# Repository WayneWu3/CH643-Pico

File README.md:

# CH643-Pico

## Introduction
The ch643-pico is a development board based on the WCH CH643Q 32-bit RISC-V MCU. It provides a compact and breadboard-friendly platform for USB Type-C and Power Delivery applications.

## Hardware Resources
*   **MCU**: WCH CH643Q featuring the QingKe-V4C RISC-V core.
*   **Interface**: USB Type-C port for power delivery and data communication.
*   **Power**: Dual power input support with 3.3V regulated output.
*   **Control**: Two user buttons and status LEDs for power and communication monitoring.
*   **Debug**: Dedicated pin headers for UART and SWD interfaces.

## Pin Definitions
| Pin | Label  | Function                   |
| :-- | :----- | :------------------------- |
| 1   | 3.3V   | 3.3V Power Output          |
| 2   | 3.3V   | 3.3V Power Output          |
| 3   | GND    | GND                        |
| 4   | PA23   | TIM2_CH3N                  |
| 5   | PA1    | TIM2_CH2/ADC_IN1           |
| 6   | PA2    | USART2_TX/TIM2_CH3/ADC_IN2 |
| 7   | PA3    | USART2_RX/TIM2_CH4/ADC_IN3 |
| 8   | GND    | GND                        |
| 9   | PA5    | SPI0_SCK/ADC_IN5           |
| 10  | PA6    | SPI0_MISO/TIM3_CH1/ADC_IN6 |
| 11  | PA7    | SPI0_MOSI/TIM3_CH2/ADC_IN7 |
| 12  | PB0    | USART4_TX/ADC_IN8          |
| 13  | PB1    | USART4_RX/ADC_IN9          |
| 14  | PB2    | TIM1_CH2N                  |
| 15  | PB3    | TIM1_CH3N                  |
| 16  | PB4    | GPIO                       |
| 17  | PB6    | TIM1_CH1N/USART3_CTS       |
| 18  | PB7    | TIM1_CH2N/USART3_RTS       |
| 19  | PB8    | TIM1_CH3N                  |
| 20  | PB9    | TIM1_CH1/MCO               |
| 21  | EXT_5V | 5V Power Input             |
| 22  | EXT_5V | 5V Power Input             |
| 23  | GND    | GND                        |
| 24  | 3.3V   | 3.3V Power Output          |
| 25  | EXT_5V | 5V Power Input             |
| 26  | PA21   | TIM2_CH1N                  |
| 27  | PA20   | TIM2_BK                    |
| 28  | GND    | GND                        |
| 29  | PA19   | TIM2_ETR                   |
| 30  | PA15   | GPIO                       |
| 31  | 3.3V   | 3.3V Power Output          |
| 32  | PA11   | I2C_SDA                    |
| 33  | GND    | GND                        |
| 34  | PA10   | I2C_SCL                    |
| 35  | PA8    | USART4_RTS                 |
| 36  | PB15   | USART4_CTS                 |
| 37  | PB23   | GPIO                       |
| 38  | GND    | GND                        |
| 39  | PB21   | GPIO                       |
| 40  | PB14   | GPIO                       |

## Onboard Peripherals
| Component   | Pin  | Logic       |
| :---------- | :--- | :---------- |
| KEY1 | PB12 | Active Low  |
| KEY2 | PB16 | Active Low  |
| LED | PB17 | Active Low |

## Functional Features
*   **Power Path**: Integrated Schottky diodes protect the circuit when using both USB and external power sources.
*   **ESD Protection**: USB data and configuration channel lines are equipped with protection arrays to ensure hardware durability.
*   **Logic Level**: All I/O signals are 3.3V compatible.

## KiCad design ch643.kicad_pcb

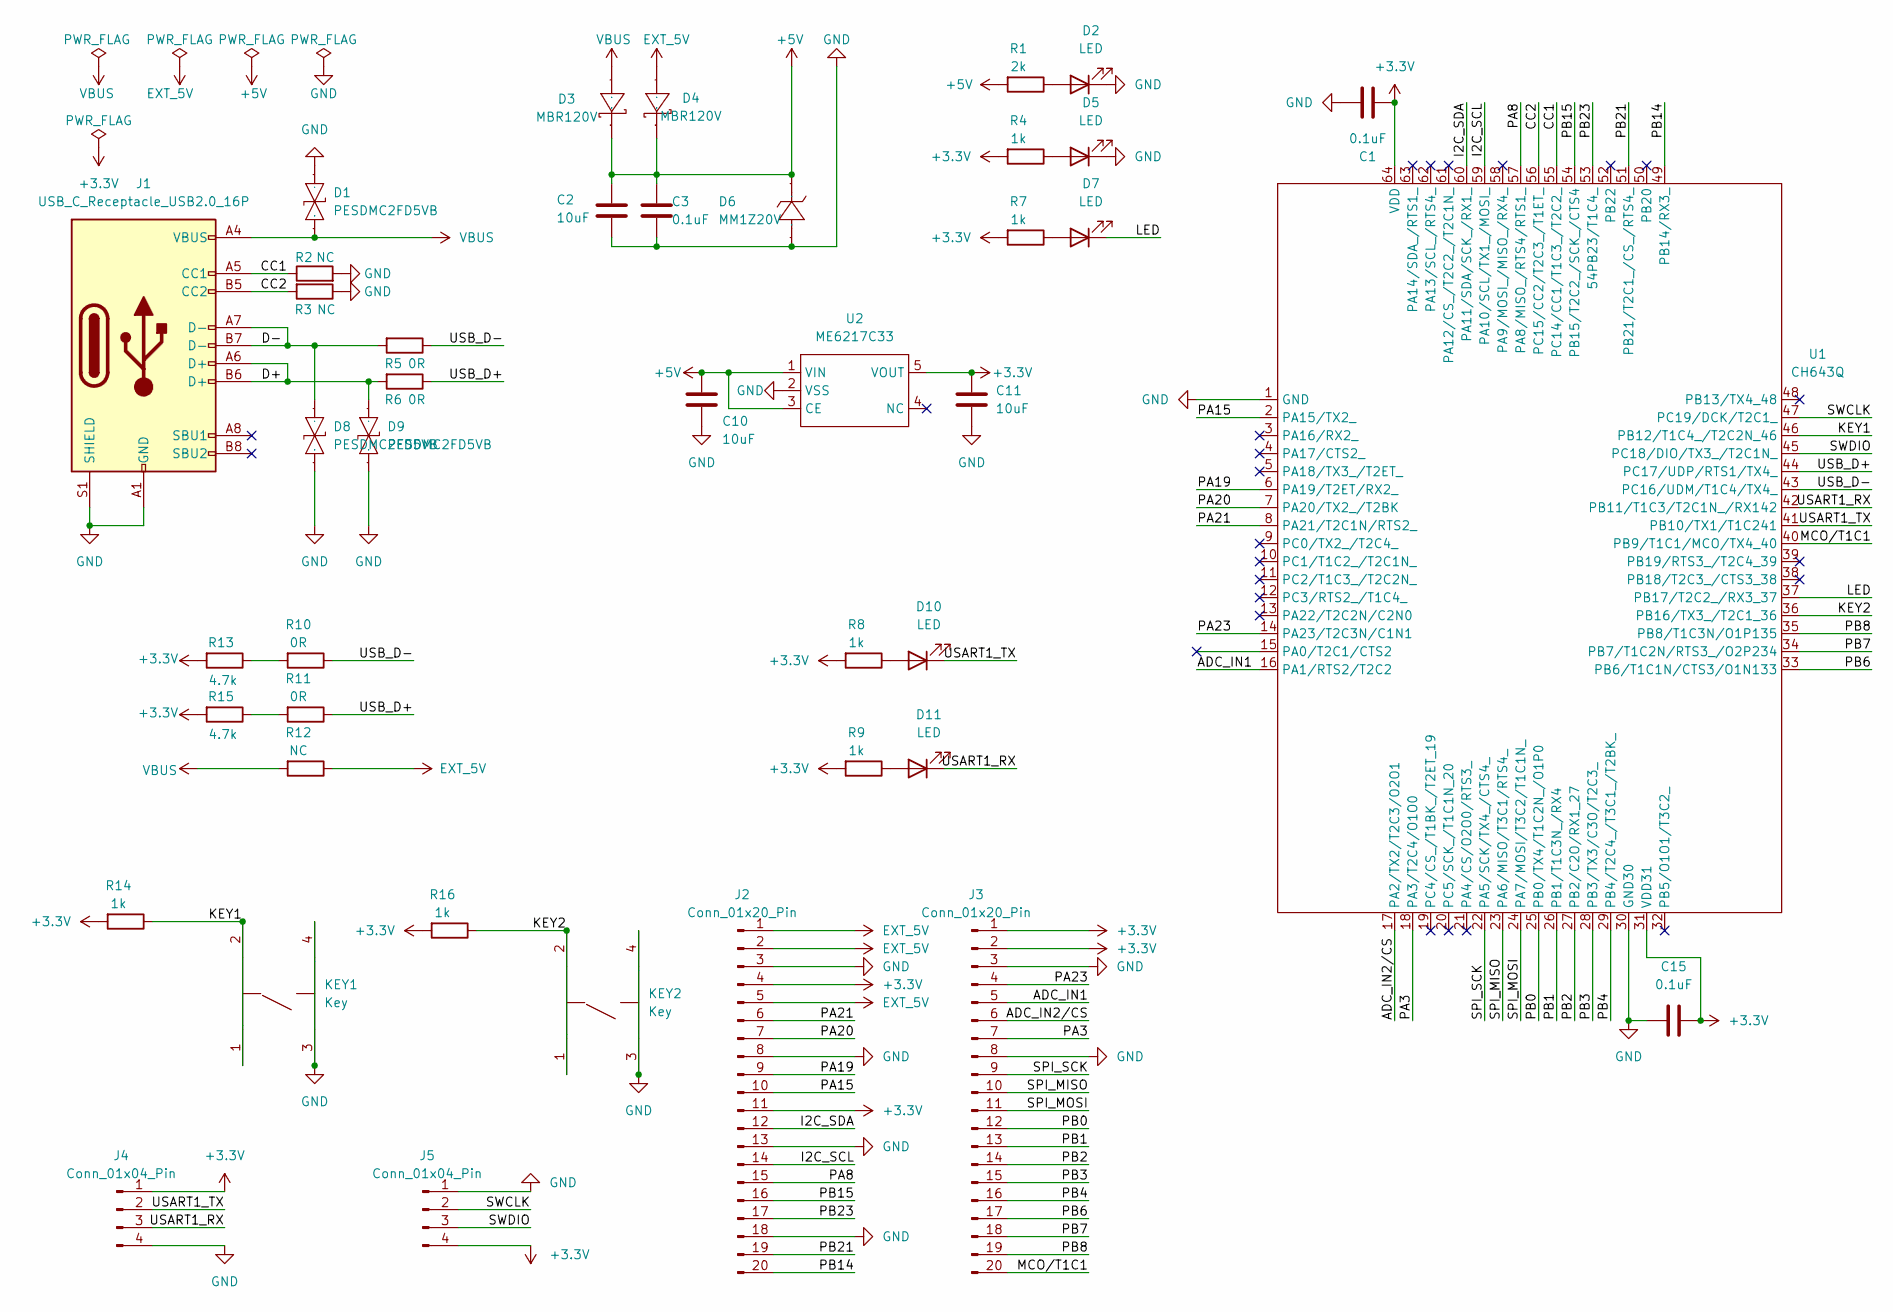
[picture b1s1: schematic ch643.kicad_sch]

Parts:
C1, C15: 0.1uF; C_0402_1005Metric
C2, C10, C11: 10uF; C_0603_1608Metric
C3: 0.1uF; C_0603_1608Metric
D1, D8, D9: PESDMC2FD5VB; DFN1006-2L-BI; Manufacturer Part PESDMC2FD5VB; LCSC Part Name 双向ESD
D2, D5, D7, D10, D11: LED; LED_0402_1005Metric
D3, D4: MBR120V; SOD-123F_L2.8-W1.8-LS3.7-RD; Manufacturer Part MBR120VLSFT1G; LCSC Part Name 电压:20V 电流:1A
D6: MM1Z20V; SOD-123_L2.8-W1.8-LS3.7-RD; Manufacturer Part MM1Z20V; LCSC Part Name MM1Z20V
J1: USB_C_Receptacle_USB2.0_16P; USB_C_Receptacle_HCTL_HC-TYPE-C-16P-01A
J2, J3: Conn_01x20_Pin; PinHeader_1x20_P2.54mm_Vertical
J4, J5: Conn_01x04_Pin; Harwin_M20-89004xx_1x04_P2.54mm_Horizontal
KEY1, KEY2: Key; SW-SMD_4P-L4.2-W3.3-P2.15-LS4.6; Manufacturer Part TSA016A2526A; LCSC Part Name 3.2*4.2*2.5H-J 260gf 白钮翘脚
R1: 2k; R_0402_1005Metric
R2, R3, R12: NC; R_0402_1005Metric
R4, R7, R8, R9, R14, R16: 1k; R_0402_1005Metric
R5, R6, R10, R11: 0R; R_0402_1005Metric
R13, R15: 4.7k; R_0402_1005Metric
U1: CH643Q; LQFP-64_L7.0-W7.0-P0.40-LS9.2-BL; Manufacturer Part CH643Q; LCSC Part Name RGB显示驱动工业级微控制器
U2: ME6217C33; SOT-23-5_L3.0-W1.7-P0.95-LS2.8-BR; Manufacturer Part ME6217C33M5G; LCSC Part Name 输入7V 输出3.3V 800mA

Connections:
+3.3V: C1.1, C11.1, C15.1, J2.4, J2.11, J3.1, J3.2, J4.1, J5.4, R4.2, R7.2, R8.2, R9.2, R13.2, R14.2, R15.2, R16.2, U1.31 (VDD31), U1.64 (VDD), U2.5 (VOUT)
+5V: C2.1, C3.1, C10.1, D3.1 (K), D4.1 (K), D6.1 (K), R1.2, U2.1 (VIN), U2.3 (CE)
/ADC_IN1: J3.5, U1.16 (PA1/RTS2/T2C2)
/ADC_IN2/CS: J3.6, U1.17 (PA2/TX2/T2C3/O2O1)
/CC1: J1.A5 (CC1), R2.1, U1.55 (PC14/CC1/T1C3_/T2C2_)
/CC2: J1.B5 (CC2), R3.2, U1.56 (PC15/CC2/T2C3_/T1ET_)
/D+: D9.2, J1.A6 (D+), J1.B6 (D+), R6.2
/D-: D8.2, J1.A7 (D-), J1.B7 (D-), R5.2
/I2C_SCL: J2.14, U1.59 (PA10/SCL/TX1_/MOSI_)
/I2C_SDA: J2.12, U1.60 (PA11/SDA/SCK_/RX1_)
/KEY1: KEY1.1, KEY1.2, R14.1, U1.46 (PB12/T1C4_/T2C2N_46)
/KEY2: KEY2.1, KEY2.2, R16.1, U1.36 (PB16/TX3_/T2C1_36)
/LED: D7.1 (K), U1.37 (PB17/T2C2_/RX3_37)
/MCO/T1C1: J3.20, U1.40 (PB9/T1C1/MCO/TX4_40)
/PA3: J3.7, U1.18 (PA3/T2C4/O1O0)
/PA8: J2.15, U1.57 (PA8/MISO_/RTS4/RTS1_)
/PA15: J2.10, U1.2 (PA15/TX2_)
/PA19: J2.9, U1.6 (PA19/T2ET/RX2_)
/PA20: J2.7, U1.7 (PA20/TX2_/T2BK)
/PA21: J2.6, U1.8 (PA21/T2C1N/RTS2_)
/PA23: J3.4, U1.14 (PA23/T2C3N/C1N1)
/PB0: J3.12, U1.25 (PB0/TX4/T1C2N_/O1P0)
/PB1: J3.13, U1.26 (PB1/T1C3N_/RX4)
/PB2: J3.14, U1.27 (PB2/C2O/RX1_27)
/PB3: J3.15, U1.28 (PB3/TX3/C3O/T2C3_)
/PB4: J3.16, U1.29 (PB4/T2C4_/T3C1_/T2BK_)
/PB6: J3.17, U1.33 (PB6/T1C1N/CTS3/O1N133)
/PB7: J3.18, U1.34 (PB7/T1C2N/RTS3_/O2P234)
/PB8: J3.19, U1.35 (PB8/T1C3N/O1P135)
/PB14: J2.20, U1.49 (PB14/RX3_)
/PB15: J2.16, U1.54 (PB15/T2C2_/SCK_/CTS4)
/PB21: J2.19, U1.51 (PB21/T2C1_/CS_/RTS4_)
/PB23: J2.17, U1.53 (54PB23/T1C4_)
/SPI_MISO: J3.10, U1.23 (PA6/MISO/T3C1/RTS4_)
/SPI_MOSI: J3.11, U1.24 (PA7/MOSI/T3C2/T1C1N_)
/SPI_SCK: J3.9, U1.22 (PA5/SCK/TX4_/CTS4_)
/SWCLK: J5.2, U1.47 (PC19/DCK/T2C1_)
/SWDIO: J5.3, U1.45 (PC18/DIO/TX3_/T2C1N_)
/USART1_RX: D11.1 (K), J4.3, U1.42 (PB11/T1C3/T2C1N_/RX142)
/USART1_TX: D10.1 (K), J4.2, U1.41 (PB10/TX1/T1C241)
/USB_D+: R6.1, R11.1, U1.44 (PC17/UDP/RTS1/TX4_)
/USB_D-: R5.1, R10.1, U1.43 (PC16/UDM/T1C4/TX4_)
EXT_5V: D4.2 (A), J2.1, J2.2, J2.5, R12.1
GND: C1.2, C2.2, C3.2, C10.2, C11.2, C15.2, D1.2, D2.1 (K), D5.1 (K), D6.2 (A), D8.1, D9.1, J1.A1 (GND), J1.A12 (GND), J1.B1 (GND), J1.B12 (GND), J1.S1 (SHIELD), J2.3, J2.8, J2.13, J2.18, J3.3, J3.8, J4.4, J5.1, KEY1.3, KEY1.4, KEY2.3, KEY2.4, R2.2, R3.1, U1.1 (GND), U1.30 (GND30), U2.2 (VSS)
unnamed: D2.2 (A), R1.1
unnamed: D5.2 (A), R4.1
unnamed: D7.2 (A), R7.1
unnamed: D10.2 (A), R8.1
unnamed: D11.2 (A), R9.1
unnamed: R10.2, R13.1
unnamed: R11.2, R15.1
VBUS: D1.1, D3.2 (A), J1.A4 (VBUS), J1.A9 (VBUS), J1.B4 (VBUS), J1.B9 (VBUS), R12.2

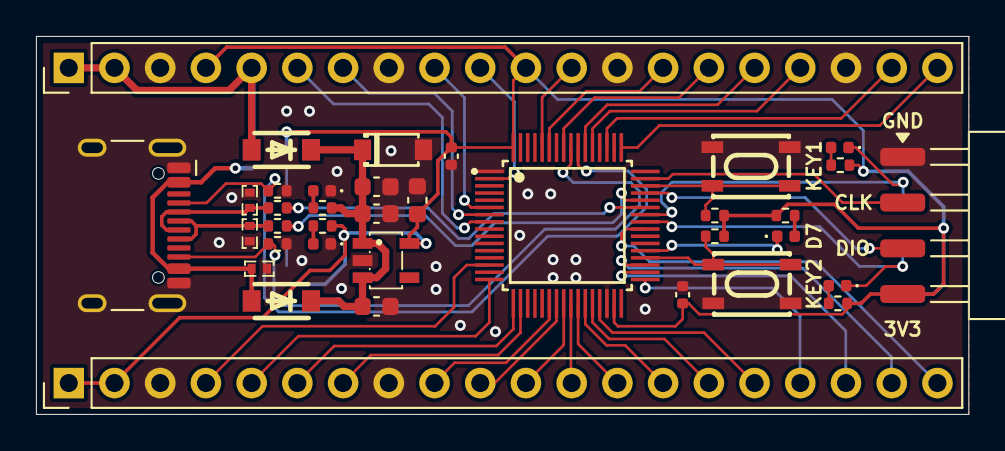
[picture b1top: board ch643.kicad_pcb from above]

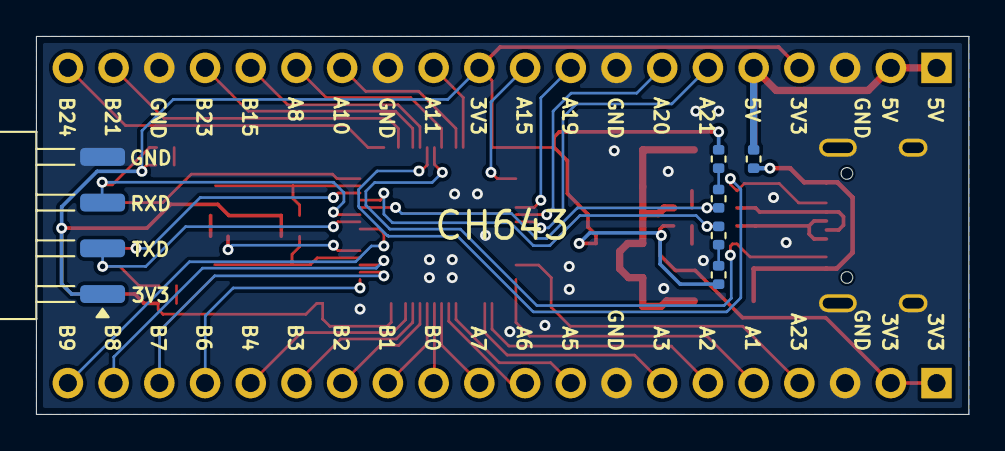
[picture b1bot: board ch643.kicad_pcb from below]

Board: 2 copper layers, 51.8 x 21.0 mm, 42 parts (6 on the bottom side), 52 nets.

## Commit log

2026-01-17 CH643-Pico in kicad
2026-01-17 Update README
    Removed Design Concept section and updated Onboard Peripherals table.
2026-01-22 feat: add 3D display
2026-01-22 docs: add 3D render of CH643 Pico
2026-01-22 docs: fix picture align
